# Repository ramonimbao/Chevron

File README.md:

# Chevron

[![CC BY-NC-SA 4.0][cc-by-nc-sa-shield]][cc-by-nc-sa]

## Through-hole 40%-ish Keyboard

Photo by bep#7432.

## Supported Layouts

## Partslist
 |Count|Part|
 |-|-|
 |1|ATmega32A 40 pin DIP|
 |1|40 pin DIP socket|
 |1|HRO-TYPE-C-M-12|
 |1|500 mA polyfuse|
 |2|6mm momentary push buttons|
 |1|16 MHz quarz crystal|
 |1|4.7 uF electrolytic capacitor|
 |2|100 nF ceramic disk capacitor|
 |2|22 pF ceramic disk capacitor|
 |2|68 Ω resistor|
 |2|1.5 kΩ resistor|
 |2|5.1 kΩ resistor|
 |2|3.6 V zener diode|
 |53|universal switching diode|
 |1|EC11 encoder and knob (optional)|

## Files

There are three folders: `bottom`, `main-pcb`, `plate`. Inside each of them are a `gerbers` production folder, and a `kicad` source folder. Grab the gerber zip files from the `gerbers` folder.

The clear cover for the components is in the `misc` folder. There's also a foot you can laser cut to be used with the bottom. Needs M2 brass standoffs or screws to use.

## Firmware

https://github.com/qmk/qmk_firmware/tree/master/keyboards/rmi_kb/chevron

## Notes

High profile case files (seen in the photo) are not provided.

The KiCAD project was made with KiCAD 5.1.4, and have not been updated.

## License 

This work is licensed under a
[Creative Commons Attribution-NonCommercial-ShareAlike 4.0 International License][cc-by-nc-sa].

This design may be freely produced, modified, and manufactured for **PERSONAL USE ONLY** and may not be reproduced in physical form for public sale.

[![CC BY-NC-SA 4.0][cc-by-nc-sa-image]][cc-by-nc-sa]

[cc-by-nc-sa]: http://creativecommons.org/licenses/by-nc-sa/4.0/
[cc-by-nc-sa-image]: https://licensebuttons.net/l/by-nc-sa/4.0/88x31.png
[cc-by-nc-sa-shield]: https://img.shields.io/badge/License-CC%20BY--NC--SA%204.0-lightgrey.svg

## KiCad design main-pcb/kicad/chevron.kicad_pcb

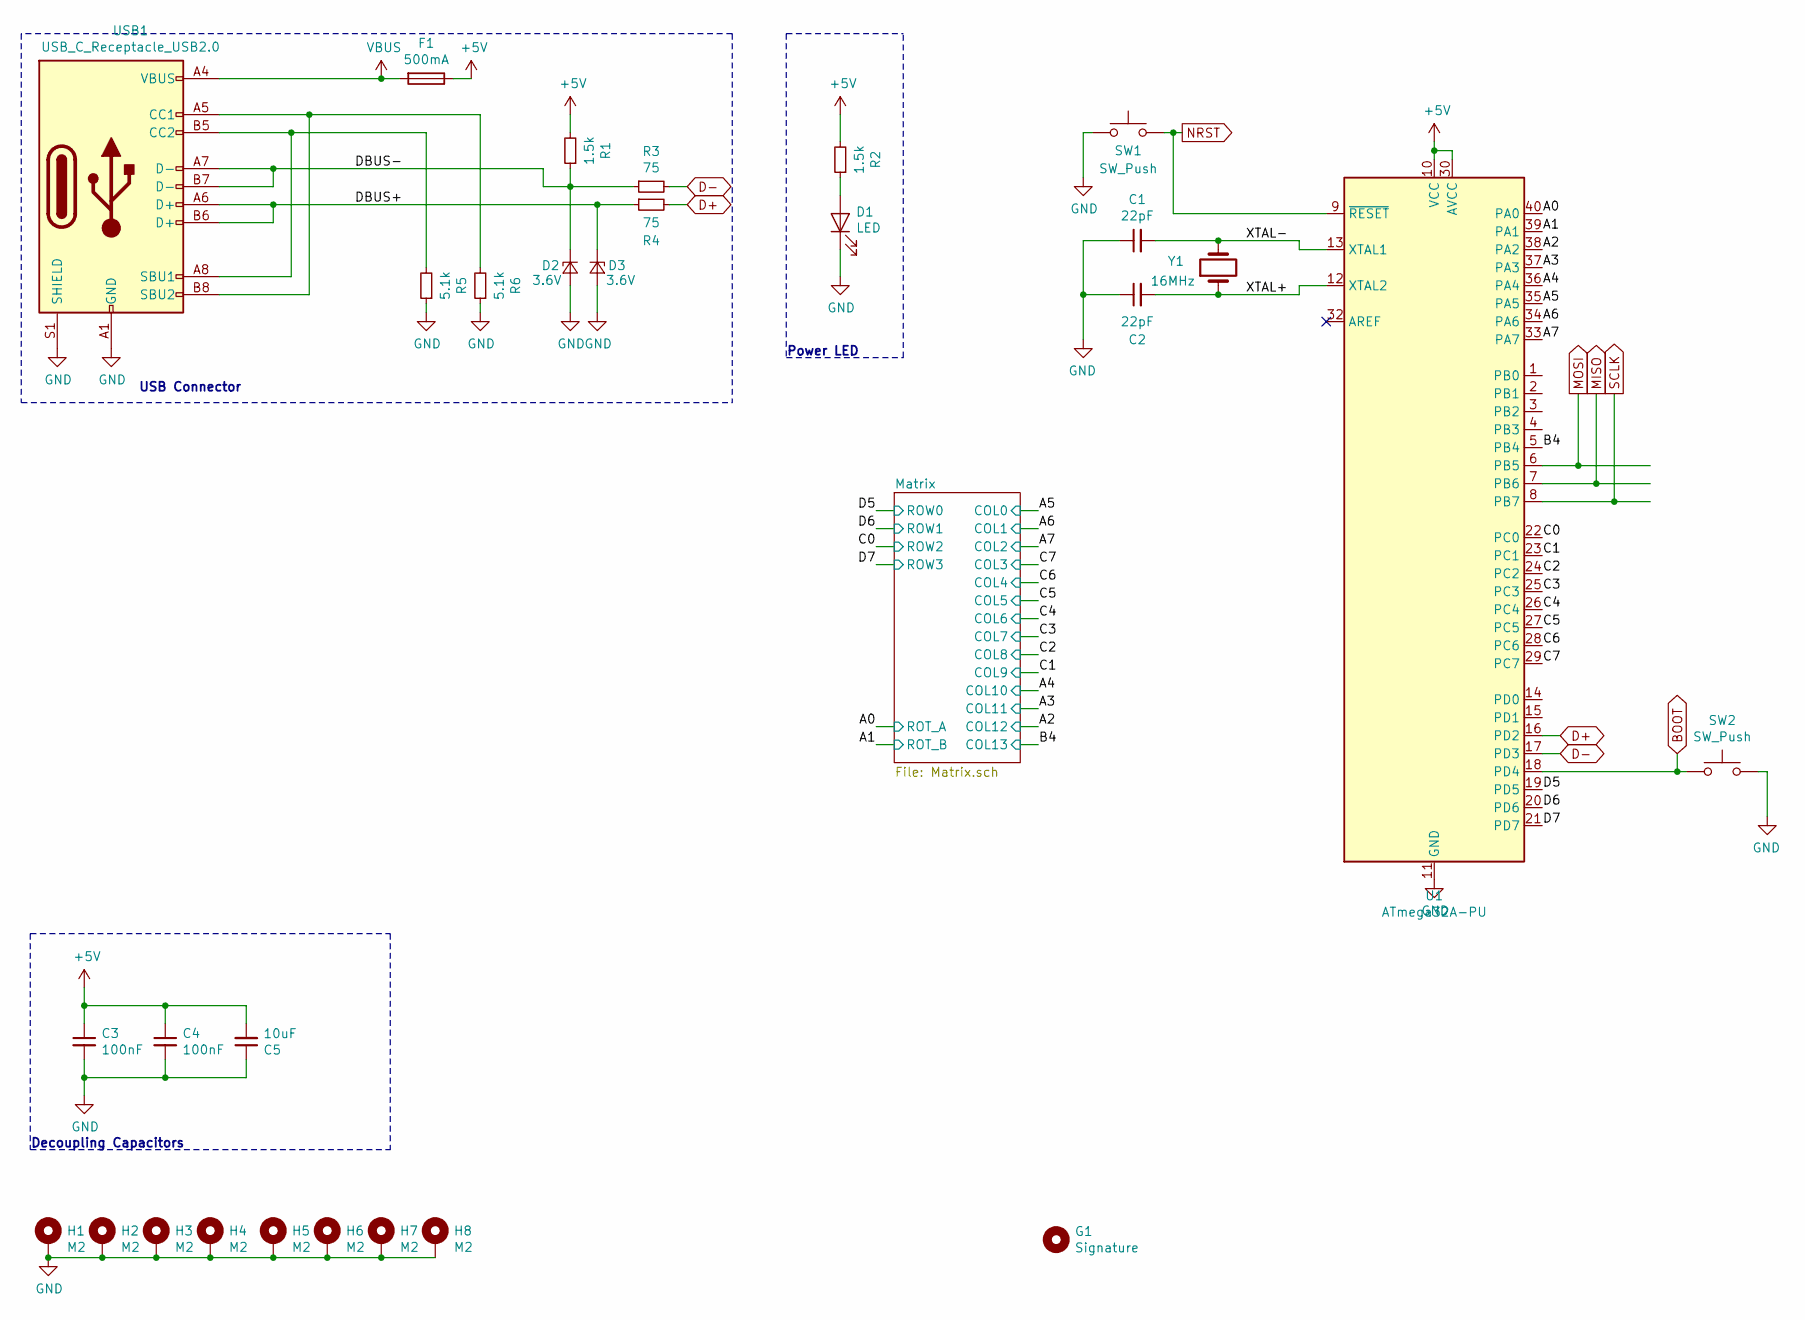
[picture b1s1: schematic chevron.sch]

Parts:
C1, C2: 22pF; C_Disc_D4.3mm_W1.9mm_P5.00mm
C3, C4: 100nF; C_Disc_D3.8mm_W2.6mm_P2.50mm
C5: 10uF; CP_Radial_D4.0mm_P1.50mm
D1: LED; LED_D3.0mm
D2, D3: 3.6V; D_DO-34_SOD68_P7.62mm_Horizontal
F1: 500mA; C_Disc_D5.0mm_W2.5mm_P5.00mm
G1: Signature
H1, H2, H3, H4, H5, H6, H7, H8: M2; MountingHole_2.2mm_M2_Pad_Via
R1, R2: 1.5k; R_Axial_DIN0204_L3.6mm_D1.6mm_P7.62mm_Horizontal
R3, R4: 75; R_Axial_DIN0204_L3.6mm_D1.6mm_P7.62mm_Horizontal
R5, R6: 5.1k; R_Axial_DIN0204_L3.6mm_D1.6mm_P7.62mm_Horizontal
SW1, SW2: SW_Push; SW_PUSH_6mm
U1: ATmega32A-PU; DIP-40_W15.24mm
USB1: USB_C_Receptacle_USB2.0; USB_C_GCT_USB4085
Y1: 16MHz; Crystal_HC49-4H_Vertical

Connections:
+5V: C3.1, C4.1, C5.2, F1.1, R1.2, R2.2, U1.10 (VCC), U1.30 (AVCC)
/A0: U1.40 (PA0); also elsewhere on the board
/A1: U1.39 (PA1); also elsewhere on the board
/A2: U1.38 (PA2); also elsewhere on the board
/A3: U1.37 (PA3); also elsewhere on the board
/A4: U1.36 (PA4); also elsewhere on the board
/A5: U1.35 (PA5); also elsewhere on the board
/A6: U1.34 (PA6); also elsewhere on the board
/A7: U1.33 (PA7); also elsewhere on the board
/B4: U1.5 (PB4); also elsewhere on the board
/C0: U1.22 (PC0); also elsewhere on the board
/C1: U1.23 (PC1); also elsewhere on the board
/C2: U1.24 (PC2); also elsewhere on the board
/C3: U1.25 (PC3); also elsewhere on the board
/C4: U1.26 (PC4); also elsewhere on the board
/C5: U1.27 (PC5); also elsewhere on the board
/C6: U1.28 (PC6); also elsewhere on the board
/C7: U1.29 (PC7); also elsewhere on the board
/D5: U1.19 (PD5); also elsewhere on the board
/D6: U1.20 (PD6); also elsewhere on the board
/D7: U1.21 (PD7); also elsewhere on the board
/DBUS+: D3.1 (K), R4.1, USB1.A6 (D+), USB1.B6 (D+)
/DBUS-: D2.1 (K), R1.1, R3.1, USB1.A7 (D-), USB1.B7 (D-)
/XTAL+: C2.2, U1.12 (XTAL2), Y1.1
/XTAL-: C1.2, U1.13 (XTAL1), Y1.2
BOOT: SW2.2, U1.18 (PD4)
D+: R4.2, U1.16 (PD2)
D-: R3.2, U1.17 (PD3)
GND: C1.1, C2.1, C3.2, C4.2, C5.1, D1.1 (K), D2.2 (A), D3.2 (A), H1.1, H2.1, H3.1, H4.1, H5.1, H6.1, H7.1, H8.1, R5.1, R6.1, SW1.1, SW2.1, U1.11 (GND), U1.31 (GND), USB1.A1 (GND), USB1.A12 (GND), USB1.B1 (GND), USB1.B12 (GND), USB1.S1 (SHIELD); also elsewhere on the board
MISO: U1.7 (PB6)
MOSI: U1.6 (PB5)
NRST: SW1.2, U1.9 (~RESET)
unnamed: D1.2 (A), R2.1
unnamed: R5.2, USB1.A8 (SBU1), USB1.B5 (CC2)
unnamed: R6.2, USB1.A5 (CC1), USB1.B8 (SBU2)
SCLK: U1.8 (PB7)
VBUS: F1.2, USB1.A4 (VBUS), USB1.A9 (VBUS), USB1.B4 (VBUS), USB1.B9 (VBUS)

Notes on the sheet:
USB Connector
Decoupling Capacitors
Power LED

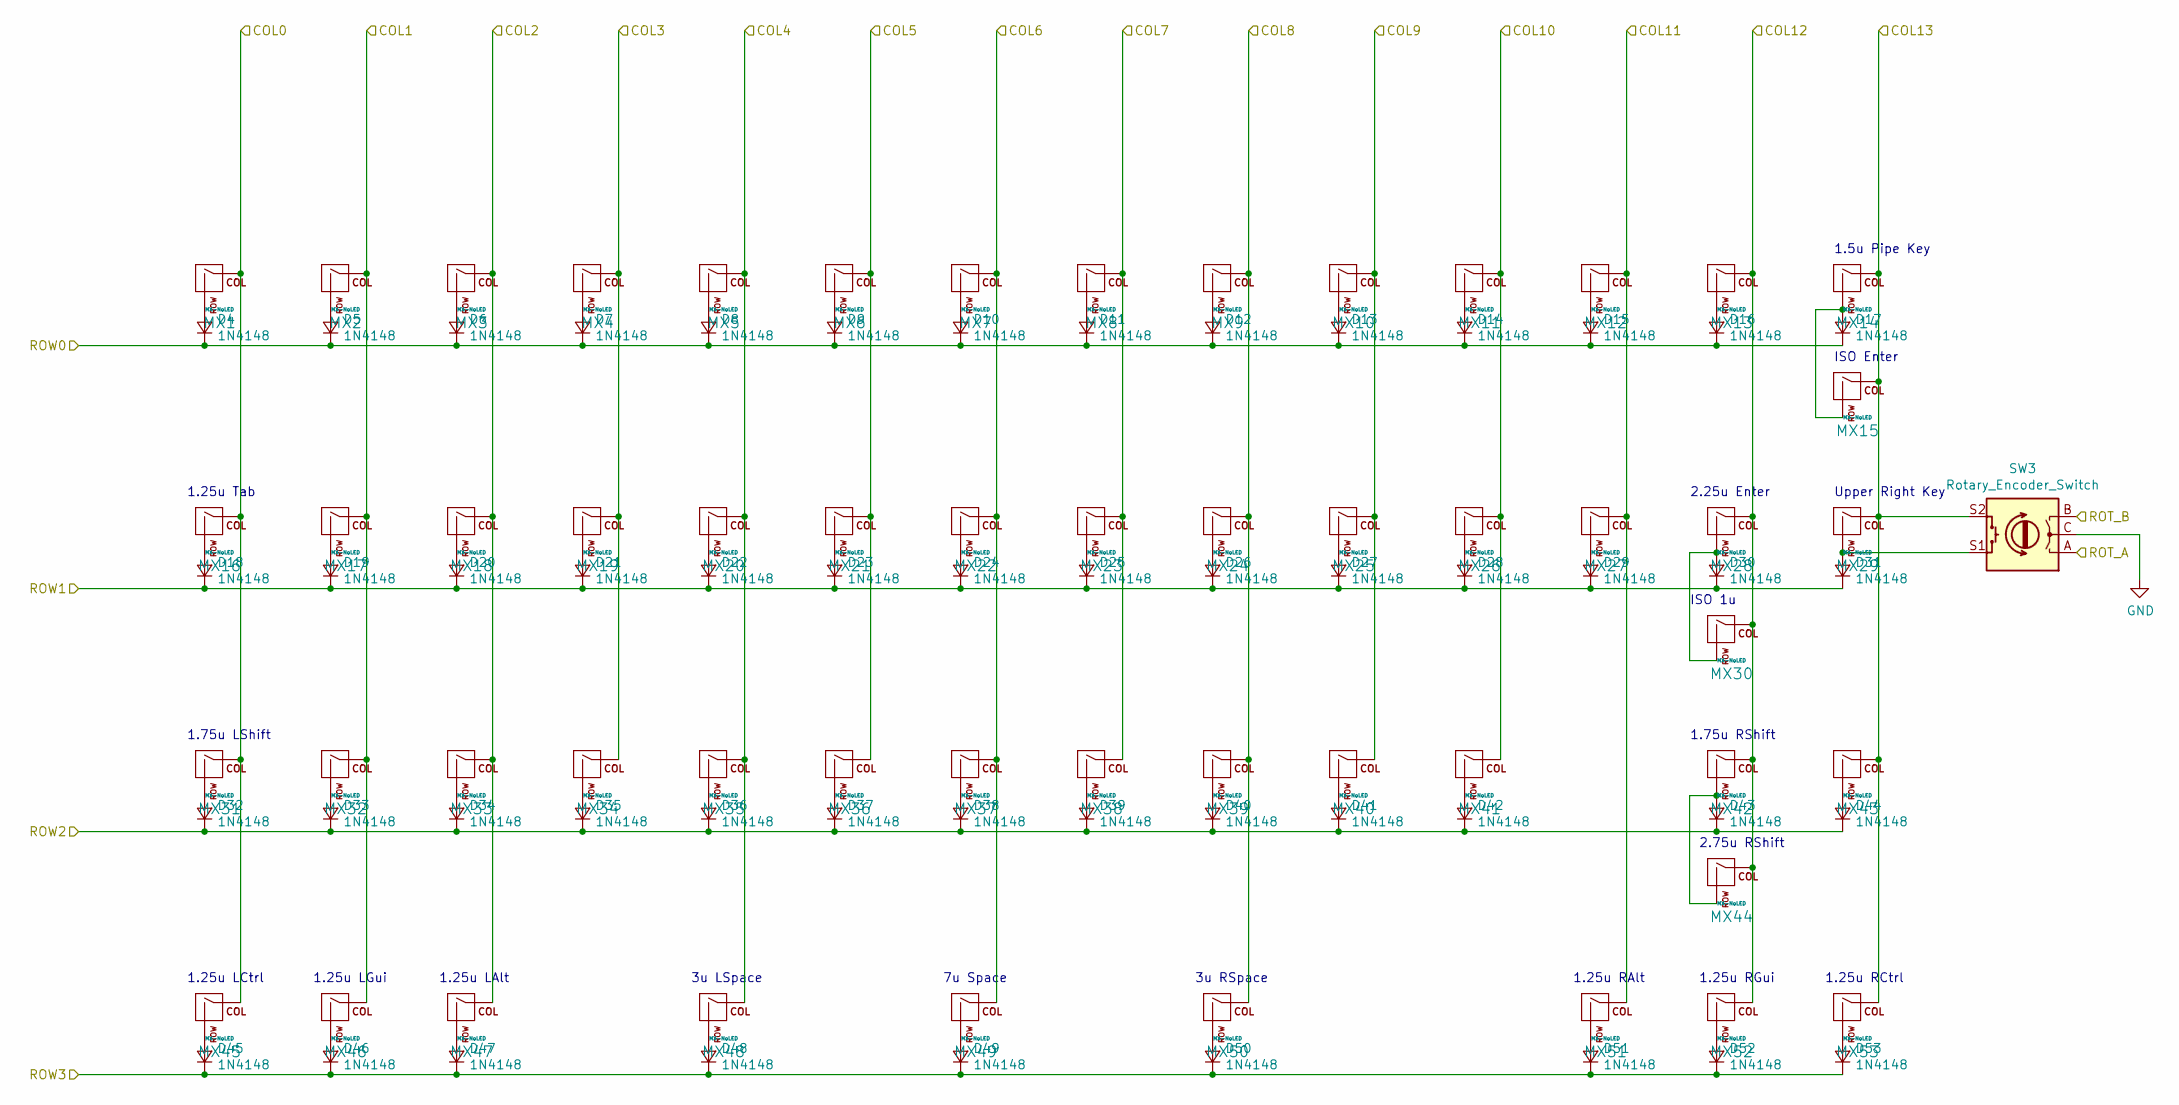
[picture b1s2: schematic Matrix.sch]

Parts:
D4, D5, D6, D7, D8, D9, D10, D11, D12, D13, D14, D15, D16, D17, D18, D19, D20, D21, D22, D23, D24, D25, D26, D27, D28, D29, D30, D31, D32, D33, D34, D35, D36, D37, D38, D39, D40, D41, D42, D43, D44, D45, D46, D47, D48, D49, D50, D51, D52, D53: 1N4148; D_DO-34_SOD68_P7.62mm_Horizontal_NoLabels
MX1, MX2, MX3, MX4, MX5, MX6, MX7, MX8, MX9, MX10, MX11, MX12, MX13, MX17, MX18, MX19, MX20, MX21, MX22, MX23, MX24, MX25, MX26, MX27, MX29, MX30, MX32, MX33, MX34, MX35, MX36, MX37, MX38, MX39, MX40, MX41, MX43: MX-NoLED; MXOnly-1U-NoLED
MX14: MX-NoLED; MXOnly-1.5U-NoLED
MX15: MX-NoLED; MXOnly-ISO-ROTATED-ReversedStabilizers-NoLED
MX16, MX45, MX46, MX47, MX51, MX52, MX53: MX-NoLED; MXOnly-1.25U-NoLED
MX28: MX-NoLED; MXOnly-2.25U-NoLED
MX31, MX42: MX-NoLED; MXOnly-1.75U-NoLED
MX44: MX-NoLED; MXOnly-2.75U-NoLED
MX48, MX50: MX-NoLED; MXOnly-3U-ReversedStabilizers-NoLED
MX49: MX-NoLED; MXOnly-7U-ReversedStabilizers-NoLED
SW3: Rotary_Encoder_Switch; RotaryEncoder_Alps_EC11E-Switch_Vertical_H20mm_Centered

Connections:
/A0: SW3.A; also elsewhere on the board
/A1: SW3.B; also elsewhere on the board
/A2: MX13.1 (COL), MX28.1 (COL), MX30.1 (COL), MX42.1 (COL), MX44.1 (COL), MX52.1 (COL); also elsewhere on the board
/A3: MX12.1 (COL), MX27.1 (COL), MX51.1 (COL); also elsewhere on the board
/A4: MX11.1 (COL), MX26.1 (COL), MX41.1 (COL); also elsewhere on the board
/A5: MX1.1 (COL), MX16.1 (COL), MX31.1 (COL), MX45.1 (COL); also elsewhere on the board
/A6: MX2.1 (COL), MX17.1 (COL), MX32.1 (COL), MX46.1 (COL); also elsewhere on the board
/A7: MX3.1 (COL), MX18.1 (COL), MX33.1 (COL), MX47.1 (COL); also elsewhere on the board
/B4: MX14.1 (COL), MX15.1 (COL), MX29.1 (COL), MX43.1 (COL), MX53.1 (COL), SW3.S2; also elsewhere on the board
/C0: D32.1 (K), D33.1 (K), D34.1 (K), D35.1 (K), D36.1 (K), D37.1 (K), D38.1 (K), D39.1 (K), D40.1 (K), D41.1 (K), D42.1 (K), D43.1 (K), D44.1 (K); also elsewhere on the board
/C1: MX10.1 (COL), MX25.1 (COL), MX40.1 (COL); also elsewhere on the board
/C2: MX9.1 (COL), MX24.1 (COL), MX39.1 (COL), MX50.1 (COL); also elsewhere on the board
/C3: MX8.1 (COL), MX23.1 (COL), MX38.1 (COL); also elsewhere on the board
/C4: MX7.1 (COL), MX22.1 (COL), MX37.1 (COL), MX49.1 (COL); also elsewhere on the board
/C5: MX6.1 (COL), MX21.1 (COL), MX36.1 (COL); also elsewhere on the board
/C6: MX5.1 (COL), MX20.1 (COL), MX35.1 (COL), MX48.1 (COL); also elsewhere on the board
/C7: MX4.1 (COL), MX19.1 (COL), MX34.1 (COL); also elsewhere on the board
/D5: D4.1 (K), D5.1 (K), D6.1 (K), D7.1 (K), D8.1 (K), D9.1 (K), D10.1 (K), D11.1 (K), D12.1 (K), D13.1 (K), D14.1 (K), D15.1 (K), D16.1 (K), D17.1 (K); also elsewhere on the board
/D6: D18.1 (K), D19.1 (K), D20.1 (K), D21.1 (K), D22.1 (K), D23.1 (K), D24.1 (K), D25.1 (K), D26.1 (K), D27.1 (K), D28.1 (K), D29.1 (K), D30.1 (K), D31.1 (K); also elsewhere on the board
/D7: D45.1 (K), D46.1 (K), D47.1 (K), D48.1 (K), D49.1 (K), D50.1 (K), D51.1 (K), D52.1 (K), D53.1 (K); also elsewhere on the board
GND: SW3.C; also elsewhere on the board
unnamed: D4.2 (A), MX1.2 (ROW)
unnamed: D5.2 (A), MX2.2 (ROW)
unnamed: D6.2 (A), MX3.2 (ROW)
unnamed: D7.2 (A), MX4.2 (ROW)
unnamed: D8.2 (A), MX5.2 (ROW)
unnamed: D9.2 (A), MX6.2 (ROW)
unnamed: D10.2 (A), MX7.2 (ROW)
unnamed: D11.2 (A), MX8.2 (ROW)
unnamed: D12.2 (A), MX9.2 (ROW)
unnamed: D13.2 (A), MX10.2 (ROW)
unnamed: D14.2 (A), MX11.2 (ROW)
unnamed: D15.2 (A), MX12.2 (ROW)
unnamed: D16.2 (A), MX13.2 (ROW)
unnamed: D17.2 (A), MX14.2 (ROW), MX15.2 (ROW)
unnamed: D18.2 (A), MX16.2 (ROW)
unnamed: D19.2 (A), MX17.2 (ROW)
unnamed: D20.2 (A), MX18.2 (ROW)
unnamed: D21.2 (A), MX19.2 (ROW)
unnamed: D22.2 (A), MX20.2 (ROW)
unnamed: D23.2 (A), MX21.2 (ROW)
unnamed: D24.2 (A), MX22.2 (ROW)
unnamed: D25.2 (A), MX23.2 (ROW)
unnamed: D26.2 (A), MX24.2 (ROW)
unnamed: D27.2 (A), MX25.2 (ROW)
unnamed: D28.2 (A), MX26.2 (ROW)
unnamed: D29.2 (A), MX27.2 (ROW)
unnamed: D30.2 (A), MX28.2 (ROW), MX30.2 (ROW)
unnamed: D31.2 (A), MX29.2 (ROW), SW3.S1
unnamed: D32.2 (A), MX31.2 (ROW)
unnamed: D33.2 (A), MX32.2 (ROW)
unnamed: D34.2 (A), MX33.2 (ROW)
unnamed: D35.2 (A), MX34.2 (ROW)
unnamed: D36.2 (A), MX35.2 (ROW)
unnamed: D37.2 (A), MX36.2 (ROW)
unnamed: D38.2 (A), MX37.2 (ROW)
unnamed: D39.2 (A), MX38.2 (ROW)
unnamed: D40.2 (A), MX39.2 (ROW)
unnamed: D41.2 (A), MX40.2 (ROW)
unnamed: D42.2 (A), MX41.2 (ROW)
unnamed: D43.2 (A), MX42.2 (ROW), MX44.2 (ROW)
unnamed: D44.2 (A), MX43.2 (ROW)
unnamed: D45.2 (A), MX45.2 (ROW)
unnamed: D46.2 (A), MX46.2 (ROW)
unnamed: D47.2 (A), MX47.2 (ROW)
unnamed: D48.2 (A), MX48.2 (ROW)
unnamed: D49.2 (A), MX49.2 (ROW)
unnamed: D50.2 (A), MX50.2 (ROW)
unnamed: D51.2 (A), MX51.2 (ROW)
unnamed: D52.2 (A), MX52.2 (ROW)
unnamed: D53.2 (A), MX53.2 (ROW)

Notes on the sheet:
ISO Enter
Upper Right Key
1.5u Pipe Key
1.25u Tab
2.25u Enter
ISO 1u
1.75u LShift
1.75u RShift
2.75u RShift
1.25u LCtrl
1.25u LGui
1.25u LAlt
3u LSpace
7u Space
3u RSpace
1.25u RAlt
1.25u RGui
1.25u RCtrl

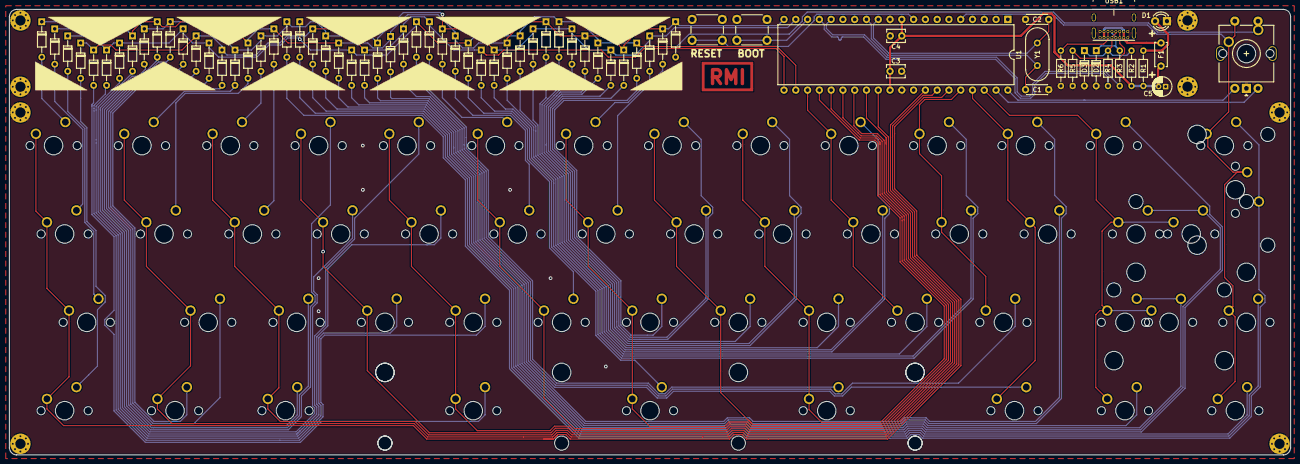
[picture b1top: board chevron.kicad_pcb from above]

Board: 2 copper layers, 276.2 x 96.0 mm, 133 parts (0 on the bottom side), 84 nets.

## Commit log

2023-05-13 Add layouts supported
